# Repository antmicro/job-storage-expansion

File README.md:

# Jetson Orin Baseboard Storage Expansion Board

Copyright (c) 2023-2025 [Antmicro](https://www.antmicro.com)

## Overview

This project contains open hardware design files for an expansion board compatible with Antmicro's [Jetson Orin Baseboard](https://github.com/antmicro/jetson-orin-baseboard).
The expansion board includes a MicroSD card slot and an M.2 (key-M) slot intended for connecting additional storage solutions to the Jetson Orin Baseboard.
It also includes an additional USB-C and USB type A connectors.
The M.2 slot supports 2280 and 2242 M.2 NVMe discs. 
The design files were prepared in KiCad 9.x.

## Key features

* Jetson Orin Baseboard expansion connector
* Support for 2280 and 2242 disc sizes
* M.2 key M
* MicroSD card reader with USB 2.0 interface
* USB-C and USB type A

## Project structure 

The main directory contains KiCad PCB project files, LICENSE, and README.
The remaining files are stored in the following directories: 
 
* `img` - contains graphics for this README

## Licensing

This project is published under the [Apache-2.0](LICENSE) license.

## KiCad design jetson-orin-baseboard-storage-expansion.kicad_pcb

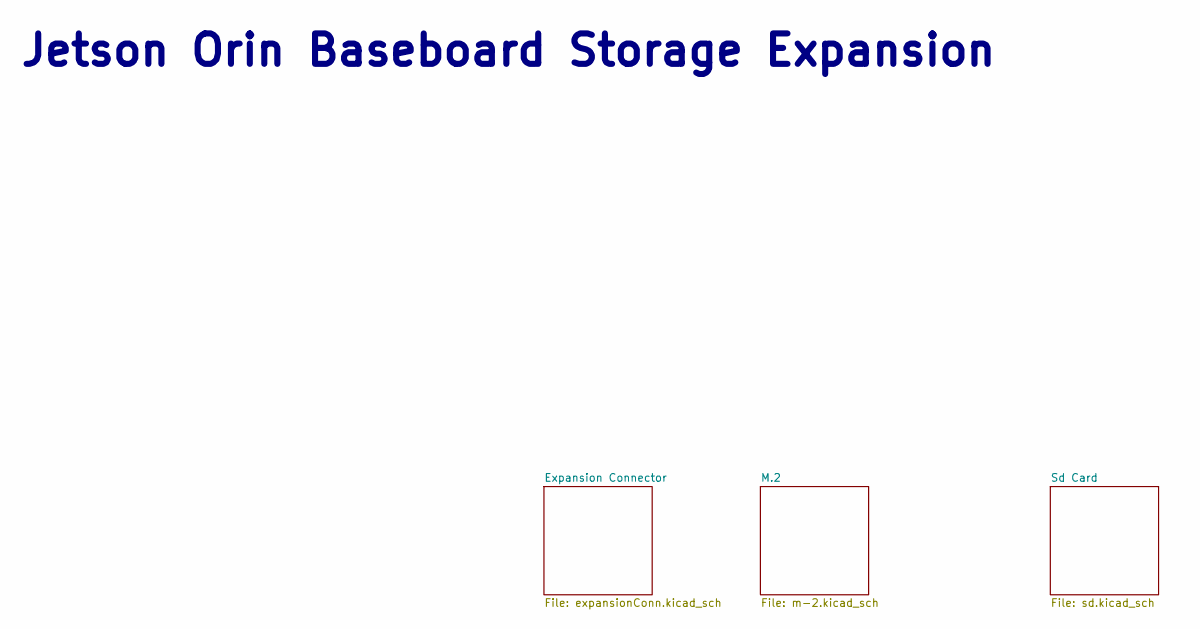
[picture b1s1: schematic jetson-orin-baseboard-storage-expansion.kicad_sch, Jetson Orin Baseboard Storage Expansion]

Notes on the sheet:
Jetson Orin Baseboard Storage Expansion

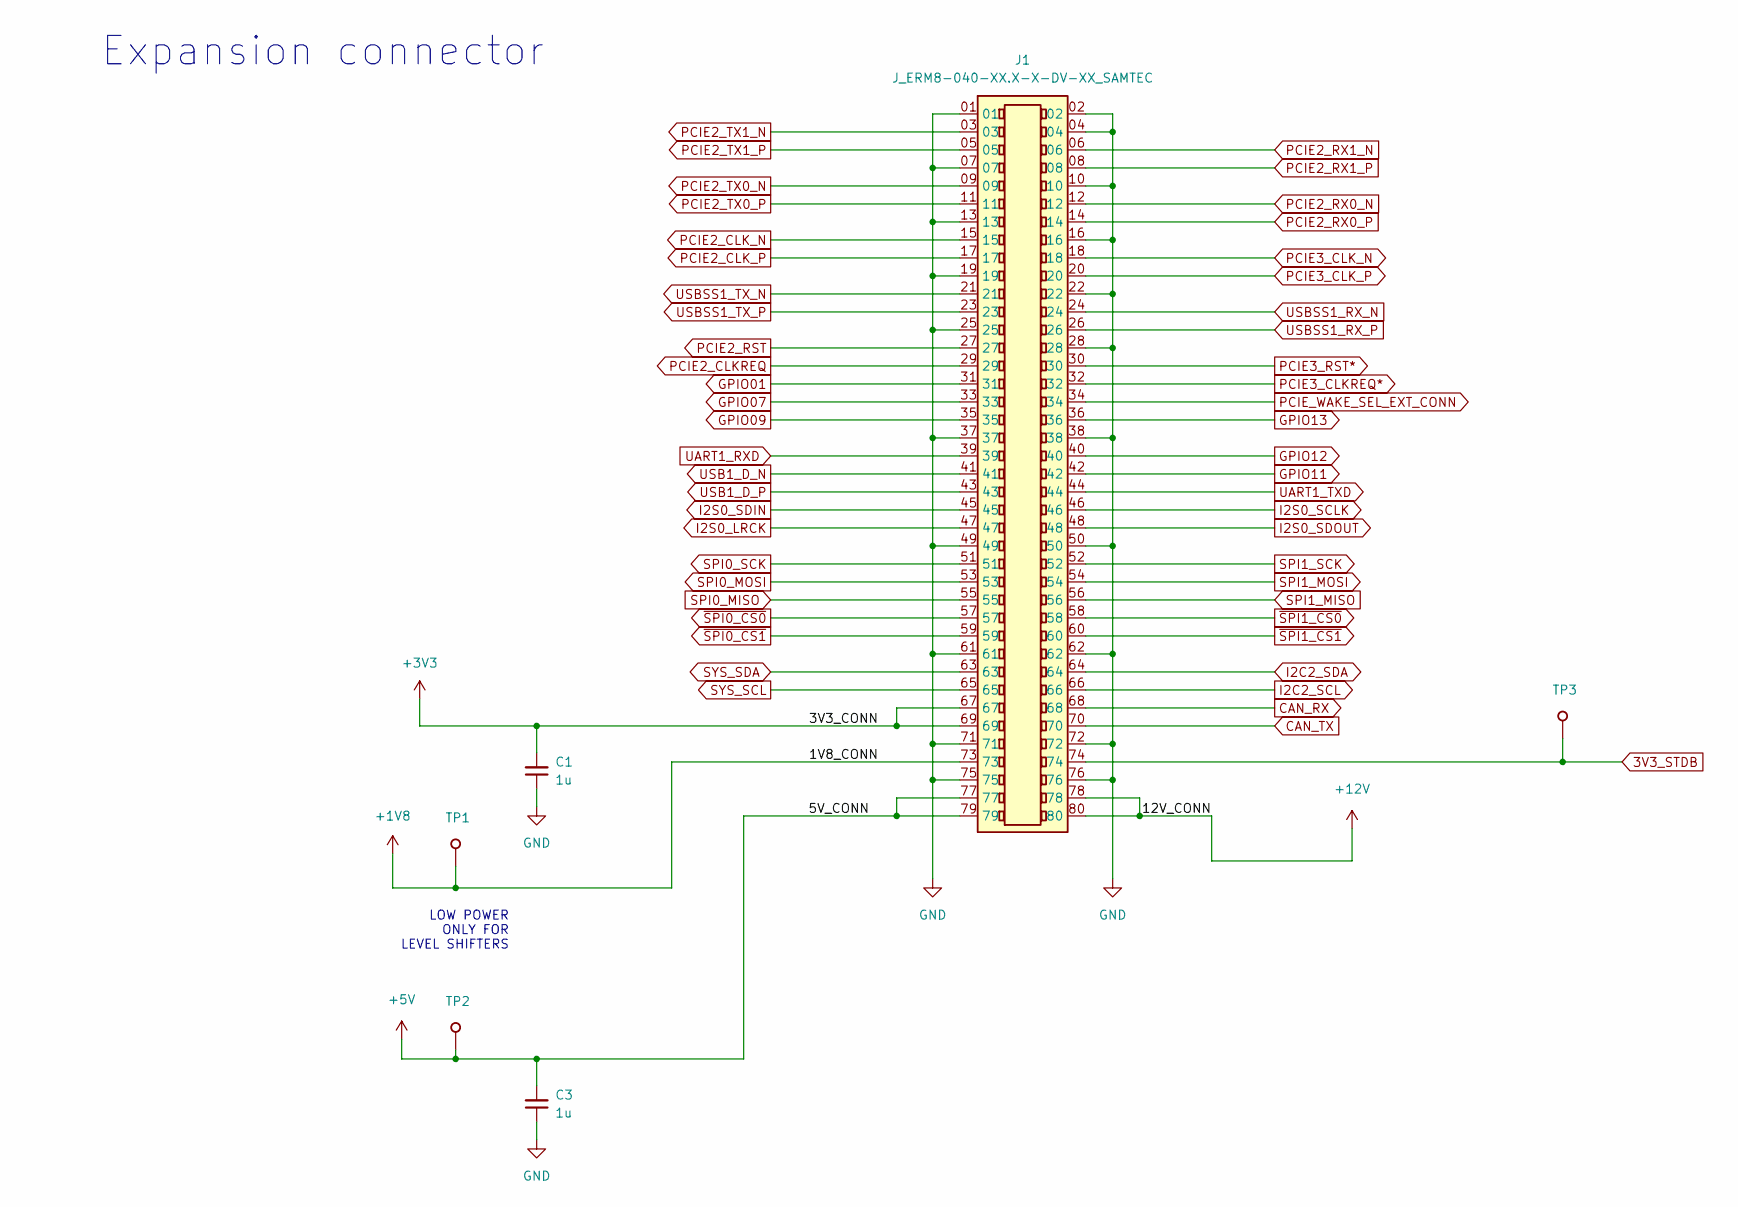
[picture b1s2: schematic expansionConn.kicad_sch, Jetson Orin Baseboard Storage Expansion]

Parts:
C1, C3: C_1u_0402; C_0402_1005Metric; MPN C1005X6S1A105K050BC
J1: J_ERM8-040-XX.X-X-DV-XX_SAMTEC; ERM8-040-05.0_SAMTEC; PARTREV J_ERM8-040-XX.X-X-DV-XX _SAMTEC
TP1, TP2, TP3: TP_1.5mm_SMD; TP_SMD_1.5mm

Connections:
3V3_STDB: J1.74, TP3.1
+1V8: J1.73, TP1.1
+3V3: C1.2, J1.67, J1.69; also elsewhere on the board
+5V: C3.2, J1.77, J1.79, TP2.1
+12V: J1.78, J1.80
CAN_RX: J1.68
CAN_TX: J1.70
GND: C1.1, C3.1, J1.01, J1.02, J1.04, J1.07, J1.10, J1.13, J1.16, J1.19, J1.22, J1.25, J1.28, J1.37, J1.38, J1.49, J1.50, J1.61, J1.62, J1.71, J1.72, J1.75, J1.76; also elsewhere on the board
GPIO01: J1.31
GPIO07: J1.33
GPIO09: J1.35
GPIO11: J1.42
GPIO12: J1.40
GPIO13: J1.36
I2C2_SCL: J1.66
I2C2_SDA: J1.64
I2S0_LRCK: J1.47
I2S0_SCLK: J1.46
I2S0_SDIN: J1.45
I2S0_SDOUT: J1.48
PCIE2_CLKREQ: J1.29; also elsewhere on the board
PCIE2_CLK_N: J1.15; also elsewhere on the board
PCIE2_CLK_P: J1.17; also elsewhere on the board
PCIE2_RST: J1.27; also elsewhere on the board
PCIE2_RX0_N: J1.12; also elsewhere on the board
PCIE2_RX0_P: J1.14; also elsewhere on the board
PCIE2_RX1_N: J1.06; also elsewhere on the board
PCIE2_RX1_P: J1.08; also elsewhere on the board
PCIE2_TX0_N: J1.09; also elsewhere on the board
PCIE2_TX0_P: J1.11; also elsewhere on the board
PCIE2_TX1_N: J1.03; also elsewhere on the board
PCIE2_TX1_P: J1.05; also elsewhere on the board
PCIE3_CLKREQ*: J1.32
PCIE3_CLK_N: J1.18
PCIE3_CLK_P: J1.20
PCIE3_RST*: J1.30
PCIE_WAKE_SEL_EXT_CONN: J1.34
SPI0_MISO: J1.55
SPI0_MOSI: J1.53
SPI0_SCK: J1.51
SPI1_MISO: J1.56
SPI1_MOSI: J1.54
SPI1_SCK: J1.52
SYS_SCL: J1.65
SYS_SDA: J1.63
UART1_RXD: J1.39
UART1_TXD: J1.44
USB1_D_N: J1.41
USB1_D_P: J1.43
USBSS1_RX_N: J1.24
USBSS1_RX_P: J1.26
USBSS1_TX_N: J1.21
USBSS1_TX_P: J1.23
~SPI0_CS0: J1.57
~SPI0_CS1: J1.59
~SPI1_CS0: J1.58
~SPI1_CS1: J1.60

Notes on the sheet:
LOW POWER ONLY FOR LEVEL SHIFTERS
Expansion connector

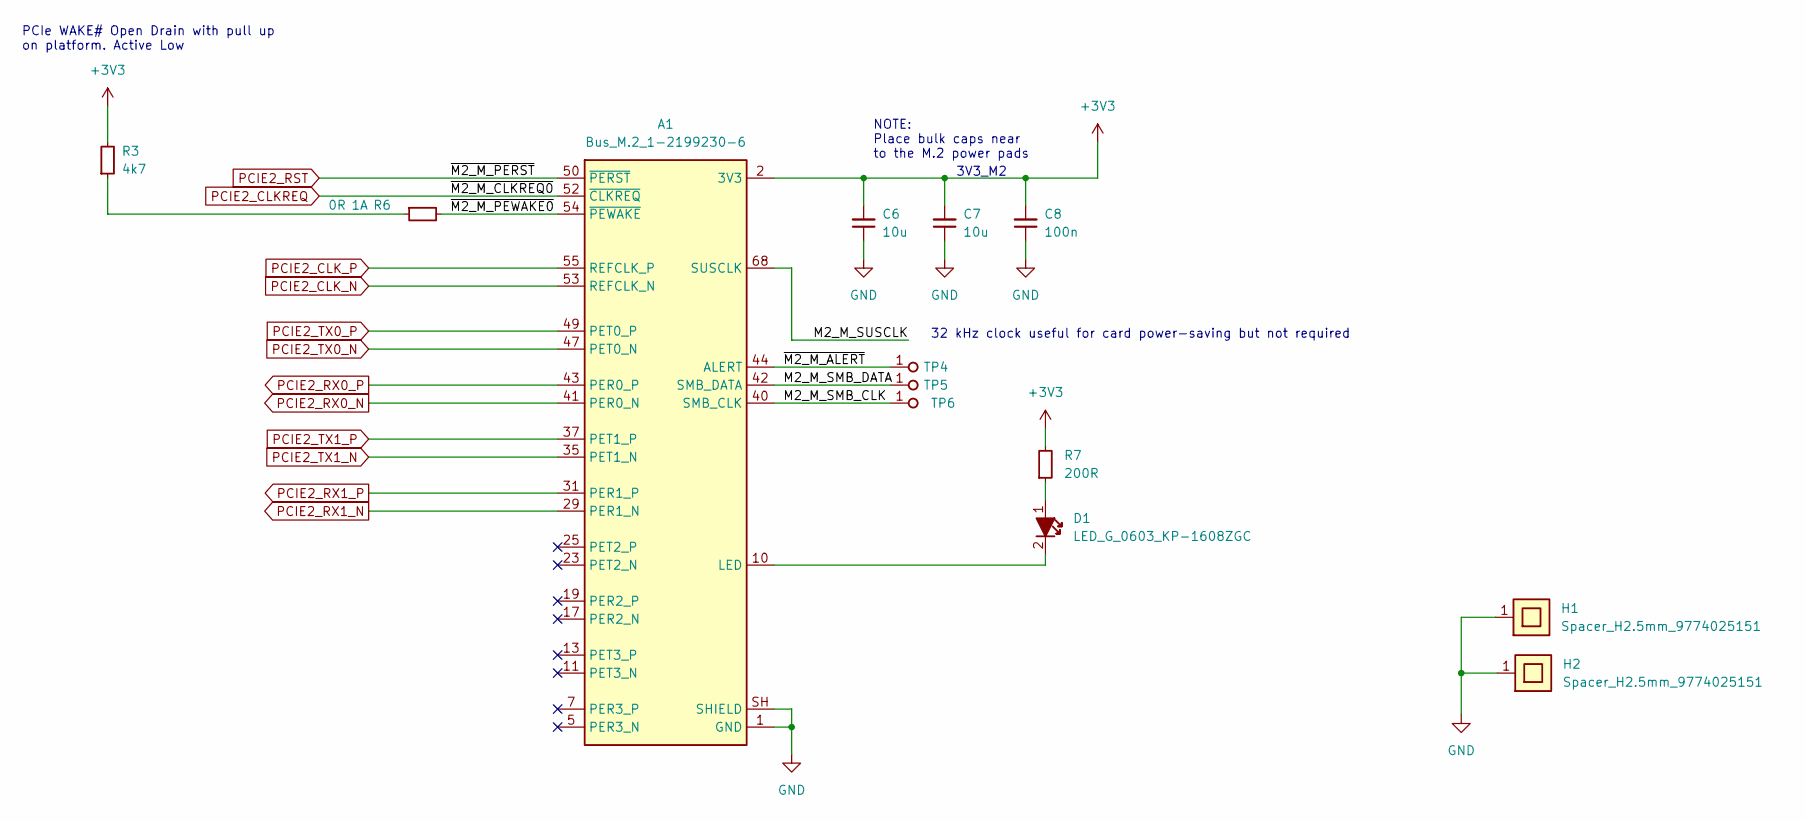
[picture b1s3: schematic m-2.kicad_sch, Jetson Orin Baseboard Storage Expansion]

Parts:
A1: Bus_M.2_1-2199230-6; Bus_M.2_Socket_Key_M_TE_1-2199230-6; MPN 1-2199230-6
C6, C7: C_10u_0402; C_0402_1005Metric; MPN CC0402MRX5R5BB106
C8: C_100n_0603; C_0603_1608Metric; MPN 0603YC104KAZ2A
D1: LED_G_0603_KP-1608ZGC; LED_0603_1608Metric_G; MPN KP-1608ZGC
H1, H2: Spacer_H2.5mm_9774025151; Spacer_SMD_M2.5_H2.5mm_Wurth_9774025151; MPN 9774025151
R3: R_4k7_0402; R_0402_1005Metric; Tolerance 1%; MPN CR0402-FX-4701GLF
R6: R_0R_0603; R_0603_1608Metric; MPN CR0603-J/-000ELF
R7: R_200R_0402; R_0402_1005Metric; Tolerance 1%; MPN CR0402-FX-2000GLF
TP4, TP5, TP6: TP_0.75mm_SMD; TP_SMD_0.75mm

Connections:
+3V3: A1.2 (3V3), A1.4 (3V3), A1.12 (3V3), A1.14 (3V3), A1.16 (3V3), A1.18 (3V3), A1.70 (3V3), A1.72 (3V3), A1.74 (3V3), C6.2, C7.2, C8.2, R3.2, R7.2; also elsewhere on the board
/M.2/M2_M_SMB_CLK: A1.40 (SMB_CLK), TP6.1
/M.2/M2_M_SMB_DATA: A1.42 (SMB_DATA), TP5.1
/M.2/M2_M_SUSCLK: A1.68 (SUSCLK)
/M.2/~M2_M_ALERT: A1.44 (ALERT), TP4.1
/M.2/~M2_M_PEWAKE0: A1.54 (~PEWAKE), R6.2
GND: A1.1 (GND), A1.3 (GND), A1.9 (GND), A1.15 (GND), A1.21 (GND), A1.27 (GND), A1.33 (GND), A1.39 (GND), A1.45 (GND), A1.51 (GND), A1.57 (GND), A1.71 (GND), A1.73 (GND), A1.75 (GND), A1.SH (SHIELD), C6.1, C7.1, C8.1, H1.1, H2.1; also elsewhere on the board
unnamed: A1.10 (LED), D1.2
unnamed: D1.1, R7.1
unnamed: R3.1, R6.1
PCIE2_CLKREQ: A1.52 (~CLKREQ); also elsewhere on the board
PCIE2_CLK_N: A1.53 (REFCLK_N); also elsewhere on the board
PCIE2_CLK_P: A1.55 (REFCLK_P); also elsewhere on the board
PCIE2_RST: A1.50 (~PERST); also elsewhere on the board
PCIE2_RX0_N: A1.41 (PER0_N); also elsewhere on the board
PCIE2_RX0_P: A1.43 (PER0_P); also elsewhere on the board
PCIE2_RX1_N: A1.29 (PER1_N); also elsewhere on the board
PCIE2_RX1_P: A1.31 (PER1_P); also elsewhere on the board
PCIE2_TX0_N: A1.47 (PET0_N); also elsewhere on the board
PCIE2_TX0_P: A1.49 (PET0_P); also elsewhere on the board
PCIE2_TX1_N: A1.35 (PET1_N); also elsewhere on the board
PCIE2_TX1_P: A1.37 (PET1_P); also elsewhere on the board

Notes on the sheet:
NOTE: Place bulk caps near to the M.2 power pads
PCIe WAKE# Open Drain with pull up on platform. Active Low
3V3_M2
32 kHz clock useful for card power-saving but not required

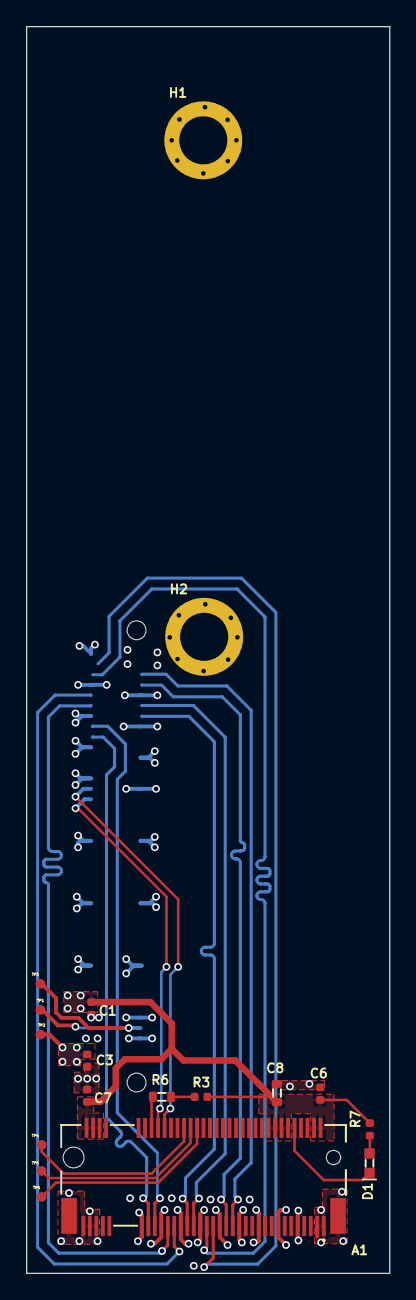
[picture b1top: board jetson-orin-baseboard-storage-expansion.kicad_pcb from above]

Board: 4 copper layers, 27.9 x 95.9 mm, 19 parts (1 on the bottom side), 25 nets.

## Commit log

2023-06-06 Create KiCad project
2023-06-07 Add layout for expansion connector and M.2 key M slot
2023-06-13 [#45539] Finish schematic + draw dif pairs and other signals
2023-06-14 [#45539] Add power traces and fix clerance DRC
2023-06-14 [#45539] Fix DRC & change via size to Eurocircuits standard
2023-06-14 [#45539] Change spacing of the m2 spacers, fix DRC, prepare labels for sd card reader
2023-10-16 [#45539] Apply changes after review
2023-10-16 Cleanup
2023-10-16 [#45990] Fix schematic flaws discussed in review
2023-10-16 [#45990] Add logos to SD sheet
2023-10-16 Add ignore
2023-10-16 [#45990] Clean up power traces
2023-10-16 [#45990] Route dif Pcie, place susclk gen
2023-10-16 [#45990] Re-arrange elements on pcb
2023-10-16 [#45990] Fix silk screen drcs
2023-10-16 [#45990] Add link to JOB repo
2023-10-16 [#45990] Fix C6 DRC
2023-10-16 [#45990} Small fix for C20
2023-10-16 [#45990] Move expansion connector, add holes for screws
2023-10-16 [#45990] Cosmetic changes for schematic, expand README
2023-10-16 [#45990] Fix texts on PCB
2023-10-16 [#45990] Route usb ic traces
2023-10-16 [#45990] Trace SDIO and 3v3 lines
2023-10-16 [#45990] Route dif USB
2023-10-16 [#45990] Rotate USB2642 for better diff usb routing
2023-10-16 Minor traces fixes
2023-10-16 [#45990] Add README
2023-10-16 [#45990] Add Blender render visualization
2023-10-16 [#45990] Link README render
2023-10-16 [#45990] Add missing components to renders
2023-10-16 [#45990] Switch VBUS_DET from VDDA to VDD33
2023-10-16 [#45990] Move board name to copper, add Rev. num
2023-10-16 Bump revision to 1.1.0
2023-10-16 Fix DRC
2023-10-16 [#45990] Remove non-sourceable elements from BOMS
2023-10-16 Fix MPN and Value on ERM8
2023-10-16 [#49775] Cleanup net lists
2023-10-16 Clean up schematic layout
2023-10-16 Remove vias-in-pads, DRC clean
2023-10-16 [#49775] Update with standarized OSHW logo
2023-10-16 Add proper PCB SHA string
2023-10-16 Adjust README to the generic format
2023-10-16 Fix misaligned M.2 connector
2023-10-16 [#49775] Update with standarized antmicro logo
2023-10-16 Alter geometry of PCIe traces to fit EC
2023-10-16 [#47315] Fix bug with SD card detect pin
2023-10-16 Resize board name
2023-10-16 Add DNP for susclk
2023-10-16 [#49775] Update mounting holes with standarized components
2023-10-16 [#49775] Update power flags
2023-10-16 Bump revision date, update PCB SHA string
2023-10-18 Add OHP assets
2023-11-07 README: describe structure
2023-11-07 README: review
2023-11-07 Add LICENSE
2024-01-16 Standardise samtech connector
2024-01-16 Fix marking mask
2024-05-23 [#56948] Update symbol/footprint links; Migrate to KiCad 7
    [#56948] Update from lib; clean DRC
    Remove Public False property from components
2024-05-23 [#56948] Update OHP assets
2024-08-19 [#64006] Moved components to the bottom. Started placement
2024-08-19 [#64006] Continued routing componentes on the bottom side
2024-08-19 [#64006] Updated footprints
2024-08-19 [#64006] Routing completed
2024-08-19 [#64006] Removed .lck file
2024-08-19 [#64006] DRC clean
2024-08-19 [#64006] Addresed all changes suggested in PCB review
2024-08-19 [#64006] Added "Not in schematic" flag to logos
2024-08-19 [#64006] Removed via in pad
2024-08-19 [#64006] Addresed all changes in review #2
2024-08-19 Revision bump to 1.1.2
2024-08-19 [#64333] Added USB-A and USB-C to the schematics
2024-09-11 [#64333] Continued routing components
2024-09-11 [#64333] Changed USB-C CC controller to FUSB303B
2024-09-11 [#64333] Added kibuzzard labels to all the ports and added PCB SHA label
2024-09-11 [#64333] Placed component references in their correct position and corrected DRC errors and warnings
2024-09-11 [#64333] First version of routing done
2024-09-11 [#64333] Added handling for USB-C CC lines and ESD protection according to review
2024-09-11 [#64333] Revision bump to 1.2.0
2024-09-11 [#64333] Fixed schematic after review
2024-09-11 [#64333] All components routed
2024-09-11 [#64333] Fixed DRC errors and started placing component references
2024-09-11 [#64333] Aligned all component references
2024-09-11 [#64333] Fixed all DRC problems and made plane for 3V3 and 5V
2024-09-11 [#64333] Tuned all high speed lines lenghs and added thermal reliefs to components that are on 3V3 and 5V planes
2024-09-11 [#64333] Fixing DRC problems and issues pinted in PCB review
2024-09-11 Updated symbols from lib. Minor DRC and ERC fixes
2024-09-11 [#64333] Rerouted components after schematics change
2024-09-11 [#64333] Added usb to net class and added via stitching
2024-09-12 Updated assets
2024-09-12 Updated README image
2024-10-15 [#67311] Replace symbol and footprint of U1, Bump revision
2024-10-15 [#67311] Fix ERC errors
2024-10-15 [#67311] Update USB footprint
2024-10-15 [#67311] Update text markings
2024-10-24 [#67311] Update assets
2024-10-28 [#67311] Update README photo and project year
2024-10-28 [#67311] Delete mention of lib folder from readme
2024-10-30 [#67311] Update assets with additional markings
2025-10-29 [#83351] Project refresh 81589

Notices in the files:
parts and their libraries:
License: Apache-2.0
